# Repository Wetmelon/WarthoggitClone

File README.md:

# WarthoggitClone
Clone of the Warthoggit Joystick PCB

### 2-Layer
* Octopart BOM: https://octopart.com/bom-tool/HYrWh7Pe
* OSHPark PCB: https://oshpark.com/shared_projects/x2CpRCvp
* Gerblook: http://gerblook.org/pcb/NEAhkPDx7kaQgrBpLWPrQZ

### 4-Layer
* Octopart BOM: https://octopart.com/bom-tool/o3ovRzzJ
* OSHPark PCB: https://oshpark.com/shared_projects/Q2SqhzfM
* Gerblook: http://gerblook.org/pcb/AL6aAQwq3UeULmAeNpxRJG

---
## Info

Uses three cascaded 8-bit parallel-to-serial shift registers, with the final downstream output hooked to an SPI MISO line.  The whole stack is clocked by the SPI CLK and latched by SPI CS.  This variant uses automotive qualified parts to withstand the vibrations expected in a joystick.

* STM HCF4021
* Panasonic 0805 package 10k ohm resistors (can be replaced with 100k if debouncing is an issue)
* 100nF 0805 capacitors, ceramic, X7R

---

## Original Reddit Post:
https://www.reddit.com/r/hoggit/comments/46pdjy/warthoggit_pcb_series_the_circuitboard_for_your/

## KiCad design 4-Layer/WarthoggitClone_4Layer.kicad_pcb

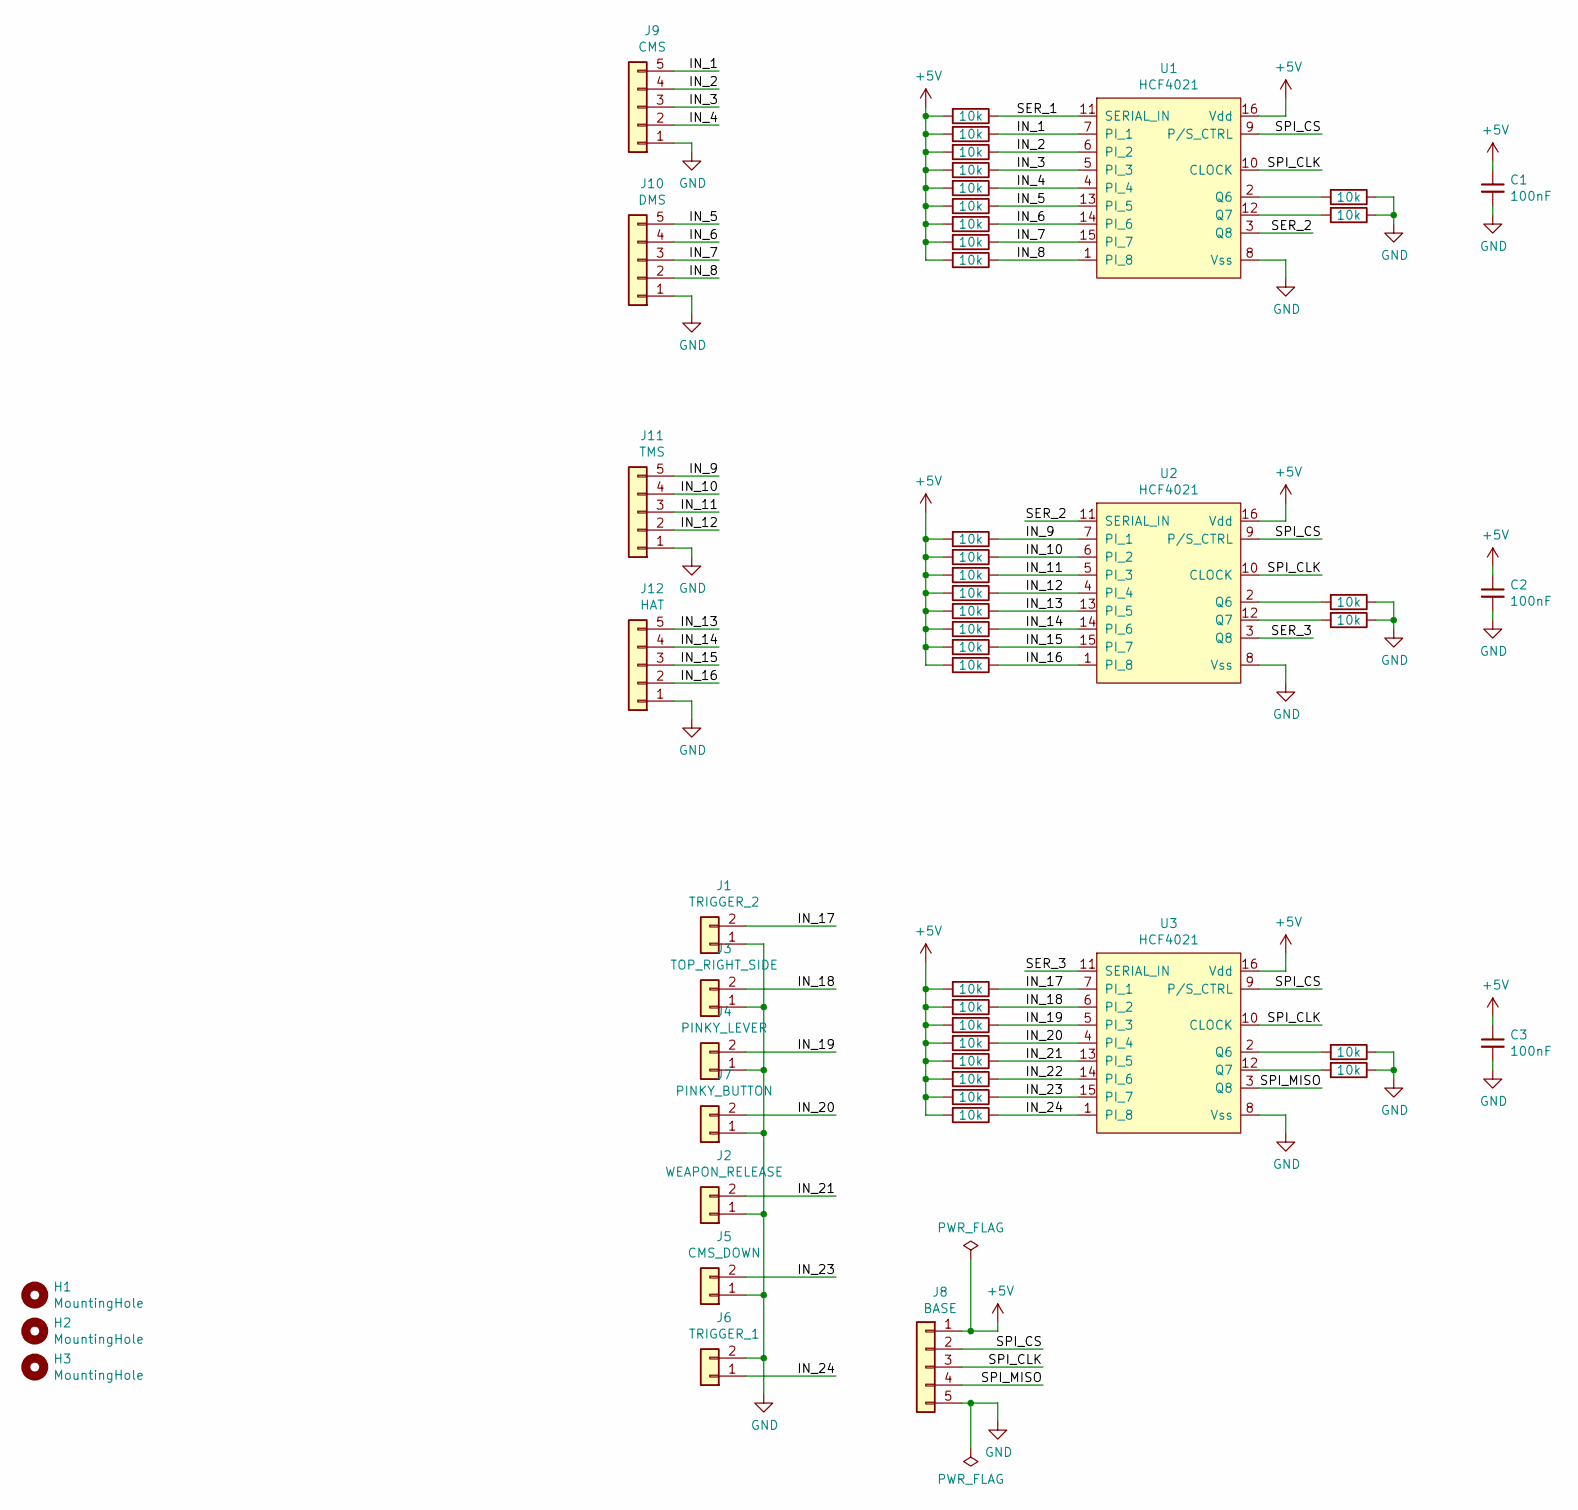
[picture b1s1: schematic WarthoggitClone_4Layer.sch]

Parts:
C1, C2, C3: 100nF; C_0805_2012Metric
H1, H2, H3: MountingHole; MountingHole_2.7mm_M2.5
J1: TRIGGER_2; Molex_PicoBlade_53047-0210_1x02_P1.25mm_Vertical
J2: WEAPON_RELEASE; Molex_PicoBlade_53047-0210_1x02_P1.25mm_Vertical
J3: TOP_RIGHT_SIDE; Molex_PicoBlade_53047-0210_1x02_P1.25mm_Vertical
J4: PINKY_LEVER; Molex_PicoBlade_53047-0210_1x02_P1.25mm_Vertical
J5: CMS_DOWN; Molex_PicoBlade_53047-0210_1x02_P1.25mm_Vertical
J6: TRIGGER_1; Molex_PicoBlade_53047-0210_1x02_P1.25mm_Vertical
J7: PINKY_BUTTON; Molex_PicoBlade_53047-0210_1x02_P1.25mm_Vertical
J8: BASE; Molex_PicoBlade_53047-0510_1x05_P1.25mm_Vertical
J9: CMS; Molex_PicoBlade_53047-0510_1x05_P1.25mm_Vertical
J10: DMS; Molex_PicoBlade_53047-0510_1x05_P1.25mm_Vertical
J11: TMS; Molex_PicoBlade_53047-0510_1x05_P1.25mm_Vertical
J12: HAT; Molex_PicoBlade_53047-0510_1x05_P1.25mm_Vertical
R1, R2, R3, R4, R5, R6, R7, R8, R9, R11, R12, R13, R14, R15, R16, R17, R18, R20, R21, R22, R23, R24, R25, R26, R27, R28, R29, R30, R31, R32, R33: 10k; R_0805_2012Metric
U1, U2, U3: HCF4021; SOIC-16_3.9x9.9mm_P1.27mm

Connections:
+5V: C1.1, C2.1, C3.1, J8.1, R1.2, R2.2, R3.2, R4.2, R5.2, R6.2, R7.2, R8.2, R9.2, R11.2, R12.2, R13.2, R14.2, R15.2, R16.2, R17.2, R18.2, R20.2, R21.2, R22.2, R23.2, R24.2, R25.2, R26.2, R27.2, U1.16 (Vdd), U2.16 (Vdd), U3.16 (Vdd)
/IN_1: J9.5, R2.1, U1.7 (PI_1)
/IN_2: J9.4, R3.1, U1.6 (PI_2)
/IN_3: J9.3, R4.1, U1.5 (PI_3)
/IN_4: J9.2, R5.1, U1.4 (PI_4)
/IN_5: J10.5, R6.1, U1.13 (PI_5)
/IN_6: J10.4, R7.1, U1.14 (PI_6)
/IN_7: J10.3, R8.1, U1.15 (PI_7)
/IN_8: J10.2, R9.1, U1.1 (PI_8)
/IN_9: J11.5, R11.1, U2.7 (PI_1)
/IN_10: J11.4, R12.1, U2.6 (PI_2)
/IN_11: J11.3, R13.1, U2.5 (PI_3)
/IN_12: J11.2, R14.1, U2.4 (PI_4)
/IN_13: J12.5, R15.1, U2.13 (PI_5)
/IN_14: J12.4, R16.1, U2.14 (PI_6)
/IN_15: J12.3, R17.1, U2.15 (PI_7)
/IN_16: J12.2, R18.1, U2.1 (PI_8)
/IN_17: J1.2, R20.1, U3.7 (PI_1)
/IN_18: J3.2, R21.1, U3.6 (PI_2)
/IN_19: J4.2, R22.1, U3.5 (PI_3)
/IN_20: J7.2, R23.1, U3.4 (PI_4)
/IN_21: J2.2, R24.1, U3.13 (PI_5)
/IN_22: R25.1, U3.14 (PI_6)
/IN_23: J5.2, R26.1, U3.15 (PI_7)
/IN_24: J6.1, R27.1, U3.1 (PI_8)
/SER_1: R1.1, U1.11 (SERIAL_IN)
/SER_2: U1.3 (Q8), U2.11 (SERIAL_IN)
/SER_3: U2.3 (Q8), U3.11 (SERIAL_IN)
/SPI_CLK: J8.3, U1.10 (CLOCK), U2.10 (CLOCK), U3.10 (CLOCK)
/SPI_CS: J8.2, U1.9 (P/S_CTRL), U2.9 (P/S_CTRL), U3.9 (P/S_CTRL)
/SPI_MISO: J8.4, U3.3 (Q8)
GND: C1.2, C2.2, C3.2, J1.1, J2.1, J3.1, J4.1, J5.1, J6.2, J7.1, J8.5, J9.1, J10.1, J11.1, J12.1, R28.1, R29.1, R30.1, R31.1, R32.1, R33.1, U1.8 (Vss), U2.8 (Vss), U3.8 (Vss)
unnamed: R28.2, U1.2 (Q6)
unnamed: R29.2, U1.12 (Q7)
unnamed: R30.2, U2.2 (Q6)
unnamed: R31.2, U2.12 (Q7)
unnamed: R32.2, U3.2 (Q6)
unnamed: R33.2, U3.12 (Q7)

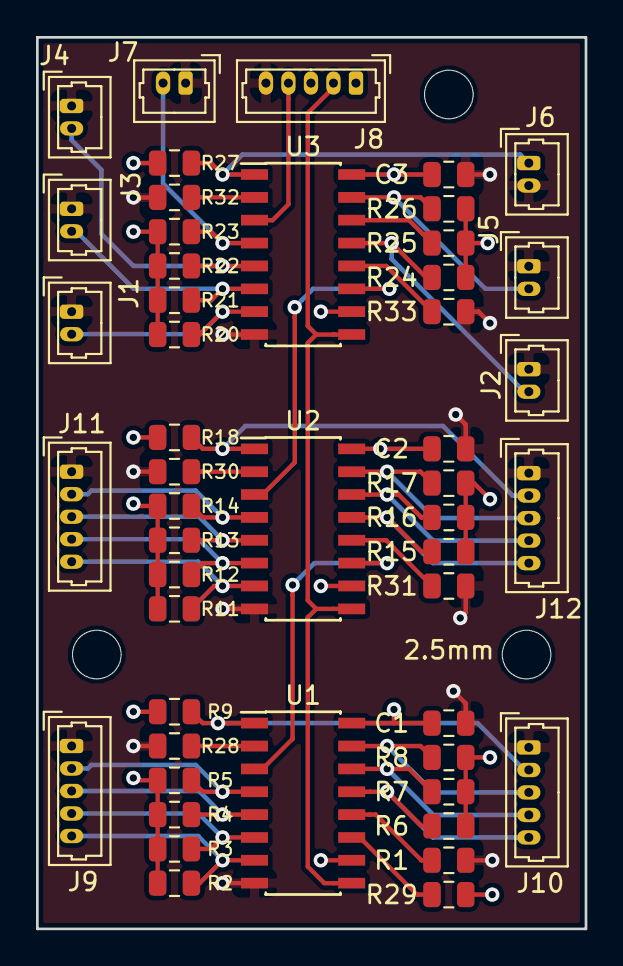
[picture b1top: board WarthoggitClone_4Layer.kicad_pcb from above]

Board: 4 copper layers, 30.5 x 49.5 mm, 52 parts (0 on the bottom side), 38 nets.

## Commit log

2018-12-28 Move Renders
2018-12-28 Create LICENSE
2018-12-28 Add Gerbers
2018-12-28 Fix DRC
2018-12-28 Add 4Layer files
2018-12-28 Split files into folders, fix missing 3D model in picoblade footprints
2018-12-28 Generate 4 layer gerbers
2018-12-28 Add zip file for 4 layer gerbers
